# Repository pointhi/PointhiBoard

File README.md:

PointhiBoard
============

A Raspberry Pi board which is optimized for standalone robotic and automation applications

**Licence:** GNU GPLv3

**work status:** still in Developing

###Required Software

* Eagle V6 or higher
* XC8-Compiler from Microchip

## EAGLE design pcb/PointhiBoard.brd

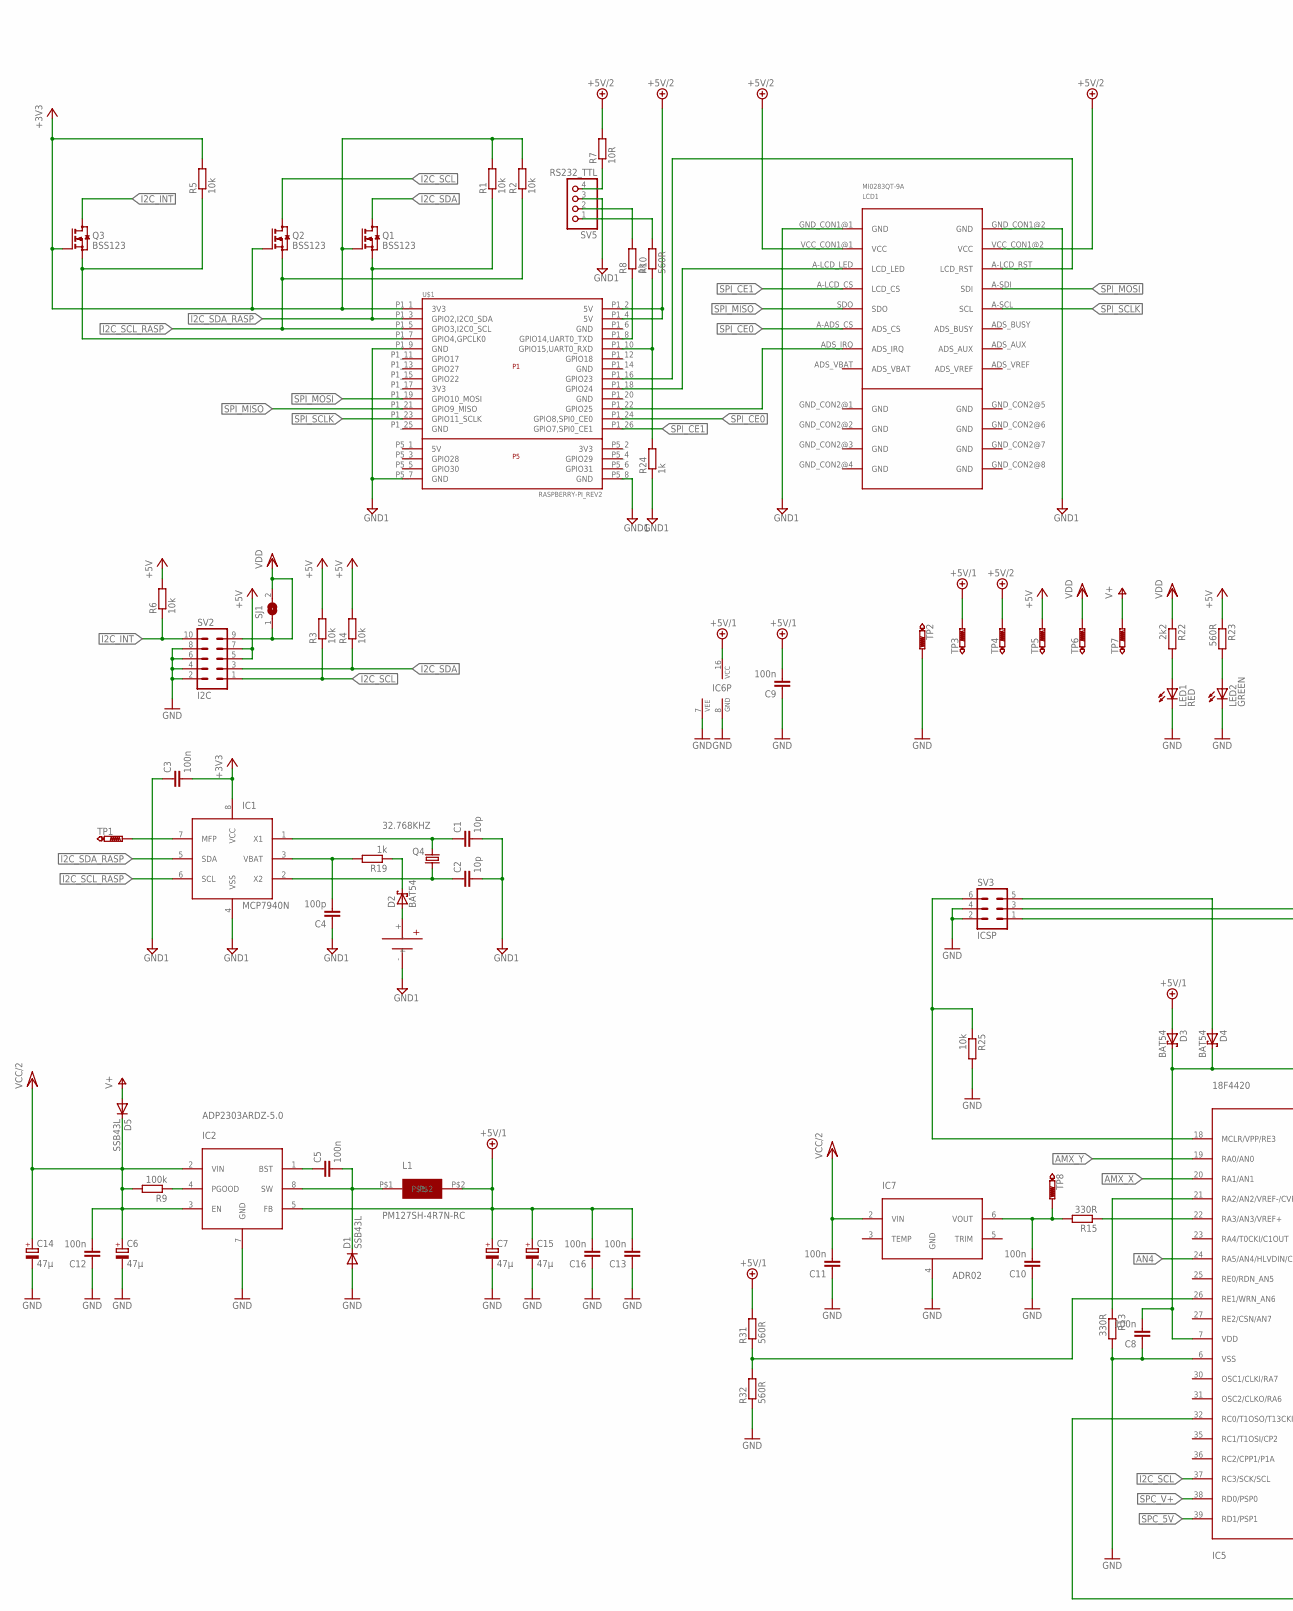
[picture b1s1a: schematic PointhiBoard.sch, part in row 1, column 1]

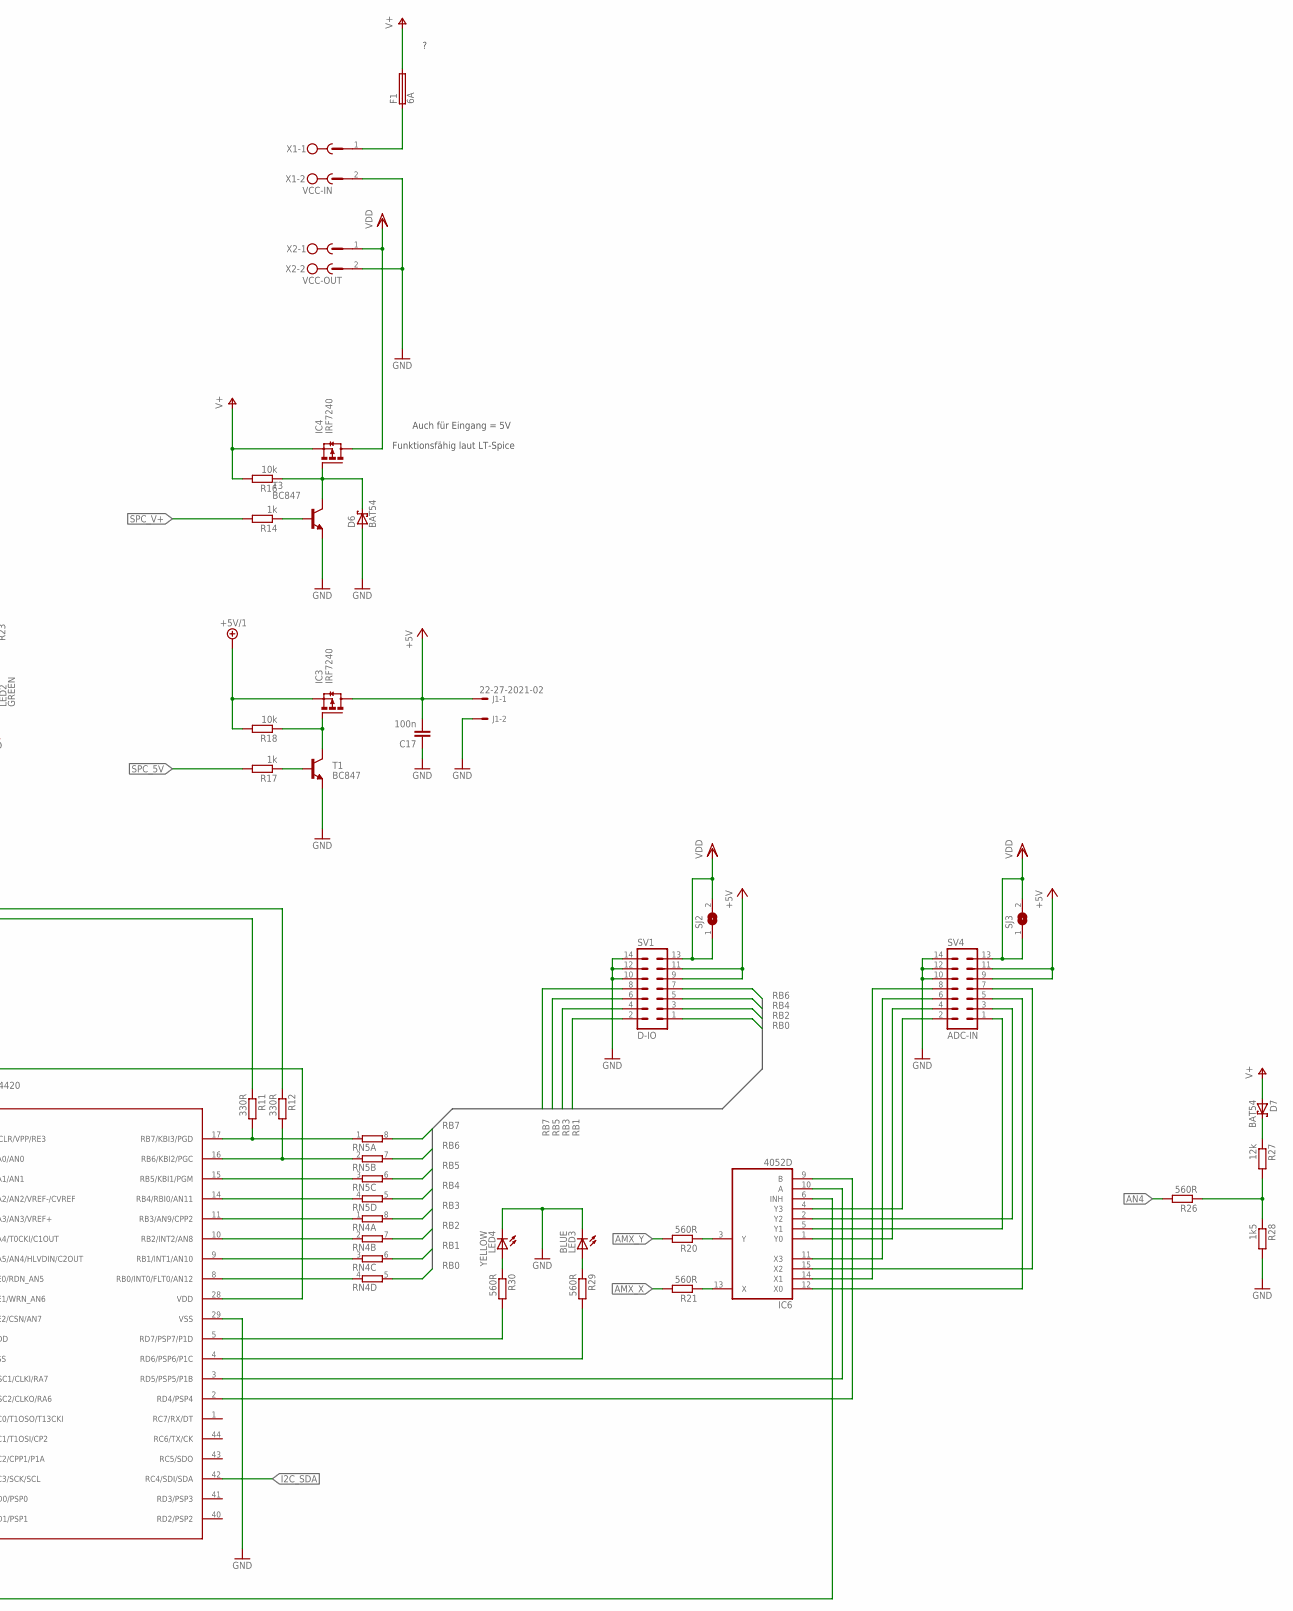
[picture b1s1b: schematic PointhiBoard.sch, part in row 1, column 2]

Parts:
BAT1: CH25-2032LF
C1, C2: 10p; C0805
C3, C5, C8, C9, C10, C11, C12, C13, C16, C17: 100n; C0805
C4: 100p; C0805
C6, C7, C14, C15: 47µ; PANASONIC_D
D1, D5: SSB43L; DO214AA
D2, D3, D4, D6, D7: BAT54; SOT23
F1: 6A; SHK20L
IC1: MCP7940N; MSOP8
IC2: ADP2303ARDZ-5.0; SOIC8
IC3, IC4: IRF7240; SOIC8
IC5: 18F4420; TQFP44
IC6: 4052D; SO16
IC7: ADR02; SOIC8
J1: 22-27-2021-02; 6410-02
L1: PM127SH-4R7N-RC; PM127SH
LCD1: MI0283QT-9A
LED1: RED; CHIP-LED0805
LED2: GREEN; CHIP-LED0805
LED3: BLUE; CHIP-LED0805
LED4: YELLOW; CHIP-LED0805
Q1, Q2, Q3: BSS123; SOT23
Q4: 32.768KHZ; MM20SS
R1, R2, R3, R4, R5, R6, R16, R18, R25: 10k; R0805
R7: 10R; R0805
R8, R14, R17, R19, R24: 1k; R0805
R9: 100k; R0805
R10, R20, R21, R23, R26, R29, R30, R31, R32: 560R; R0805
R11, R12, R13, R15: 330R; R0805
R22: 2k2; R0805
R27: 12k; R0805
R28: 1k5; R0805
RN4, RN5: 4R-NEXB38V; EXB38V
SJ1, SJ2, SJ3: SJ
SV1: D-IO; 3M_14L
SV2: I2C; 3M_10L
SV3: ICSP; ML6
SV4: ADC-IN; 3M_14L
SV5: RS232_TTL; 1X04
T1, T3: BC847; SOT23
TP1, TP2, TP3, TP4, TP5, TP6, TP7, TP8: PTR1B2,54; B2,54
U$1: RASPBERRY-PI_REV2
X1: VCC-IN; MSTBV2
X2: VCC-OUT; MSTBV2

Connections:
+3V3: C3.2, IC1.8 (VCC), Q1.1 (G), Q2.1 (G), Q3.1 (G), R1.2, R2.2, R5.2, U$1.P1_1 (3V3)
+5V: C17.2, IC3.5 (D), IC3.6 (D), IC3.7 (D), IC3.8 (D), J1.1, R3.2, R4.2, R6.2, R23.1, SV1.9, SV1.11, SV2.5, SV2.7, SV4.9, SV4.11, TP5.TP
+5V/1: C7.+, C9.2, C13.2, C15.+, C16.2, D3.1 (A), IC2.5 (FB), IC3.1 (S), IC3.2 (S), IC3.3 (S), IC6.16 (VCC), L1.P$2, R18.2, R31.2, TP3.TP
+5V/2: LCD1.VCC_CON1@1 (VCC), LCD1.VCC_CON1@2 (VCC), R7.2, TP4.TP, U$1.P1_2 (5V), U$1.P1_4 (5V)
AMX_X: IC5.20 (RA1/AN1), R21.2
AMX_Y: IC5.19 (RA0/AN0), R20.2
AN4: IC5.24 (RA5/AN4/HLVDIN/C2OUT), R26.2
GND: C6.-, C7.-, C8.1, C9.1, C10.1, C11.1, C12.1, C13.1, C14.-, C15.-, C16.1, C17.1, D1.A, D6.1 (A), IC2.7 (GND), IC5.6 (VSS), IC5.29 (VSS), IC6.7 (VEE), IC6.8 (GND), IC7.4 (GND), J1.2, LED1.C, LED2.C, LED3.C, LED4.C, R13.2, R25.2, R28.2, R32.1, SV1.10, SV1.12, SV1.14, SV2.2, SV2.4, SV2.6, SV2.8, SV3.2, SV3.4, SV4.10, SV4.12, SV4.14, T1.2 (E), T3.2 (E), TP2.TP, X1.2, X2.2
GND1: BAT1.-, C1.2, C2.2, C3.1, C4.1, IC1.4 (VSS), LCD1.GND_CON1@1 (GND), LCD1.GND_CON1@2 (GND), R24.1, SV5.3, U$1.P1_9 (GND), U$1.P5_7 (GND), U$1.P5_8 (GND)
I2C_INT: Q3.3 (D), R6.1, SV2.10
I2C_SCL: IC5.37 (RC3/SCK/SCL), Q2.3 (D), R3.1, SV2.1
I2C_SCL_RASP: IC1.6 (SCL), Q2.2 (S), R2.1, U$1.P1_5 (GPIO3,I2C0_SCL)
I2C_SDA: IC5.42 (RC4/SDI/SDA), Q1.3 (D), R4.1, SV2.3
I2C_SDA_RASP: IC1.5 (SDA), Q1.2 (S), R1.1, U$1.P1_3 (GPIO2,I2C0_SDA)
MCLR: IC5.18 (MCLR/VPP/RE3), R25.1, SV3.6
unnamed: Q3.2 (S), R5.1, U$1.P1_7 (GPIO4,GPCLK0)
unnamed: LCD1.A-LCD_LED (LCD_LED), U$1.P1_18 (GPIO24)
unnamed: LCD1.A-LCD_RST (LCD_RST), U$1.P1_16 (GPIO23)
unnamed: LCD1.ADS_IRQ, U$1.P1_22 (GPIO25)
unnamed: R7.1, SV5.4
unnamed: R8.1, U$1.P1_8 (GPIO14,UART0_TXD)
unnamed: R8.2, SV5.2
unnamed: C5.2, D1.C, IC2.8 (SW), L1.P$1
unnamed: C8.2, D3.3 (C), D4.3 (C), IC5.7 (VDD), IC5.28 (VDD)
unnamed: C5.1, IC2.1 (BST)
unnamed: IC2.4 (PGOOD), R9.1
unnamed: IC5.17 (RB7/KBI3/PGD), R11.2, RN5.1
unnamed: IC5.16 (RB6/KBI2/PGC), R12.2, RN5.2 (1)
unnamed: C1.1, IC1.1 (X1), Q4.1
unnamed: C2.1, IC1.2 (X2), Q4.4 (2)
unnamed: D6.3 (C), IC4.4 (G), R16.1, T3.3 (C)
unnamed: R14.1, T3.1 (B)
unnamed: IC1.7 (MFP), TP1.TP
unnamed: IC5.15 (RB5/KBI1/PGM), RN5.3 (1)
unnamed: IC3.4 (G), R18.1, T1.3 (C)
unnamed: R17.1, T1.1 (B)
unnamed: IC5.14 (RB4/RBI0/AN11), RN5.4 (1)
unnamed: IC5.11 (RB3/AN9/CPP2), RN4.1
unnamed: F1.1A (1), X1.1
unnamed: IC5.10 (RB2/INT2/AN8), RN4.2 (1)
unnamed: IC5.9 (RB1/INT1/AN10), RN4.3 (1)
unnamed: IC5.8 (RB0/INT0/FLT0/AN12), RN4.4 (1)
unnamed: D4.1 (A), SV3.5
unnamed: C4.2, IC1.3 (VBAT), R19.2
unnamed: BAT1.+, D2.1 (A)
unnamed: D2.3 (C), R19.1
unnamed: D7.3 (C), R27.1
unnamed: R11.1, SV3.1
unnamed: R12.1, SV3.3
unnamed: IC6.1 (Y0), SV4.4
unnamed: IC6.2 (Y2), SV4.3
unnamed: IC6.4 (Y3), SV4.2
unnamed: IC6.5 (Y1), SV4.1
unnamed: IC6.15 (X2), SV4.7
unnamed: IC6.14 (X1), SV4.8
unnamed: IC6.12 (X0), SV4.5
unnamed: IC6.11 (X3), SV4.6
unnamed: IC5.3 (RD5/PSP5/P1B), IC6.10 (A)
unnamed: IC5.2 (RD4/PSP4), IC6.9 (B)
unnamed: IC5.32 (RC0/T1OSO/T13CKI), IC6.6 (INH)
unnamed: C10.2, IC7.6 (VOUT), R15.2, TP8.TP
unnamed: IC5.22 (RA3/AN3/VREF+), R15.1
unnamed: IC5.21 (RA2/AN2/VREF-/CVREF), R13.1
unnamed: IC6.13 (X), R21.1
unnamed: IC6.3 (Y), R20.1
unnamed: LED1.A, R22.2
unnamed: LED2.A, R23.2
unnamed: R10.1, R24.2, U$1.P1_10 (GPIO15,UART0_RXD)
unnamed: R10.2, SV5.1
unnamed: R26.1, R27.2, R28.1
unnamed: IC5.4 (RD6/PSP6/P1C), R29.2
unnamed: IC5.26 (RE1/WRN_AN6), R31.1, R32.2
unnamed: IC5.5 (RD7/PSP7/P1D), R30.2
unnamed: LED3.A, R29.1
unnamed: LED4.A, R30.1
RB0: RN4.5 (2), SV1.1
RB1: RN4.6 (2), SV1.2
RB2: RN4.7 (2), SV1.3
RB3: RN4.8 (2), SV1.4
RB4: RN5.5 (2), SV1.5
RB5: RN5.6 (2), SV1.6
RB6: RN5.7 (2), SV1.7
RB7: RN5.8 (2), SV1.8
SPC_5V: IC5.39 (RD1/PSP1), R17.2
SPC_V+: IC5.38 (RD0/PSP0), R14.2
SPI_CE0: LCD1.A-ADS_CS (ADS_CS), U$1.P1_24 (GPIO8,SPI0_CE0)
SPI_CE1: LCD1.A-LCD_CS (LCD_CS), U$1.P1_26 (GPIO7,SPI0_CE1)
SPI_MISO: LCD1.SDO, U$1.P1_21 (GPIO9_MISO)
SPI_MOSI: LCD1.A-SDI (SDI), U$1.P1_19 (GPIO10_MOSI)
SPI_SCLK: LCD1.A-SCL (SCL), U$1.P1_23 (GPIO11_SCLK)
V+: D5.A, D7.1 (A), F1.2A (2), IC4.1 (S), IC4.2 (S), IC4.3 (S), R16.2, TP7.TP
VCC/2: C6.+, C11.2, C12.2, C14.+, D5.C, IC2.2 (VIN), IC2.3 (EN), IC7.2 (VIN), R9.2
VDD: IC4.5 (D), IC4.6 (D), IC4.7 (D), IC4.8 (D), R22.1, SJ1.1, SJ1.2, SJ2.1, SJ2.2, SJ3.1, SJ3.2, SV1.13, SV2.9, SV4.13, TP6.TP, X2.1

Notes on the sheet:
Funktionsfähig laut LT-Spice
Auch für Eingang = 5V

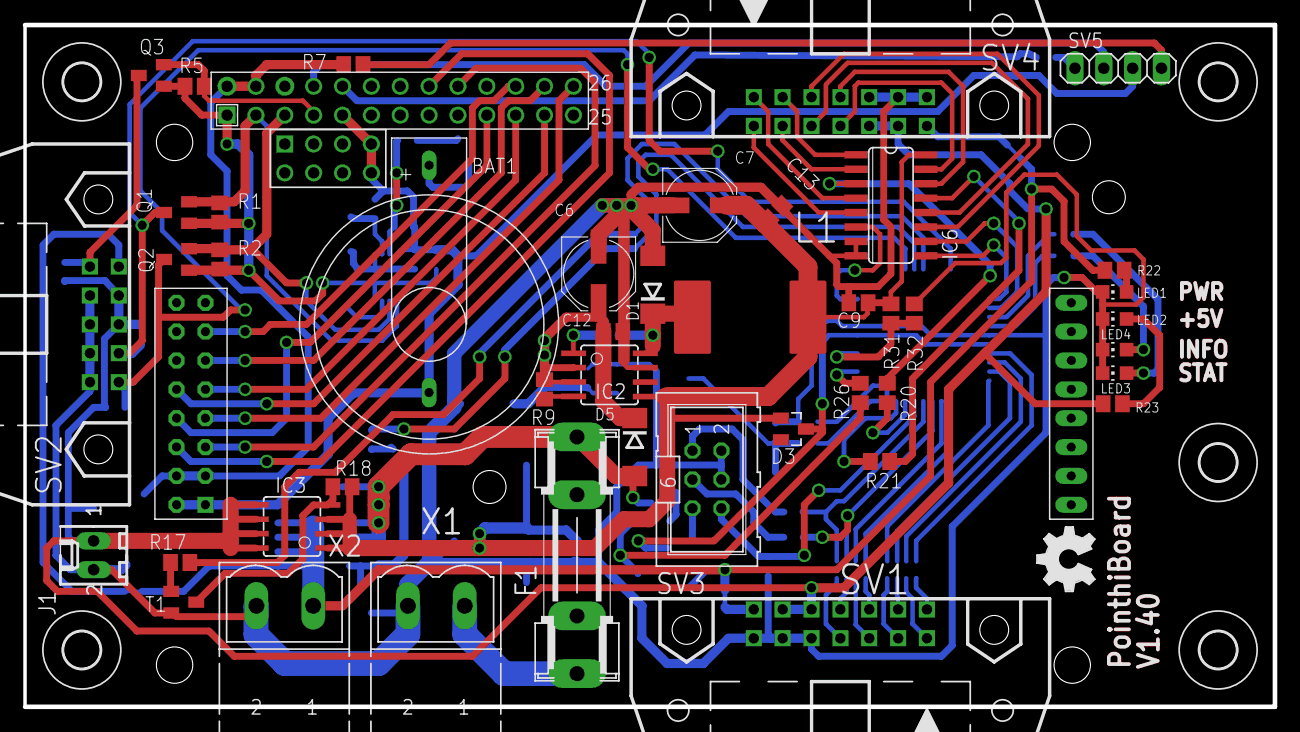
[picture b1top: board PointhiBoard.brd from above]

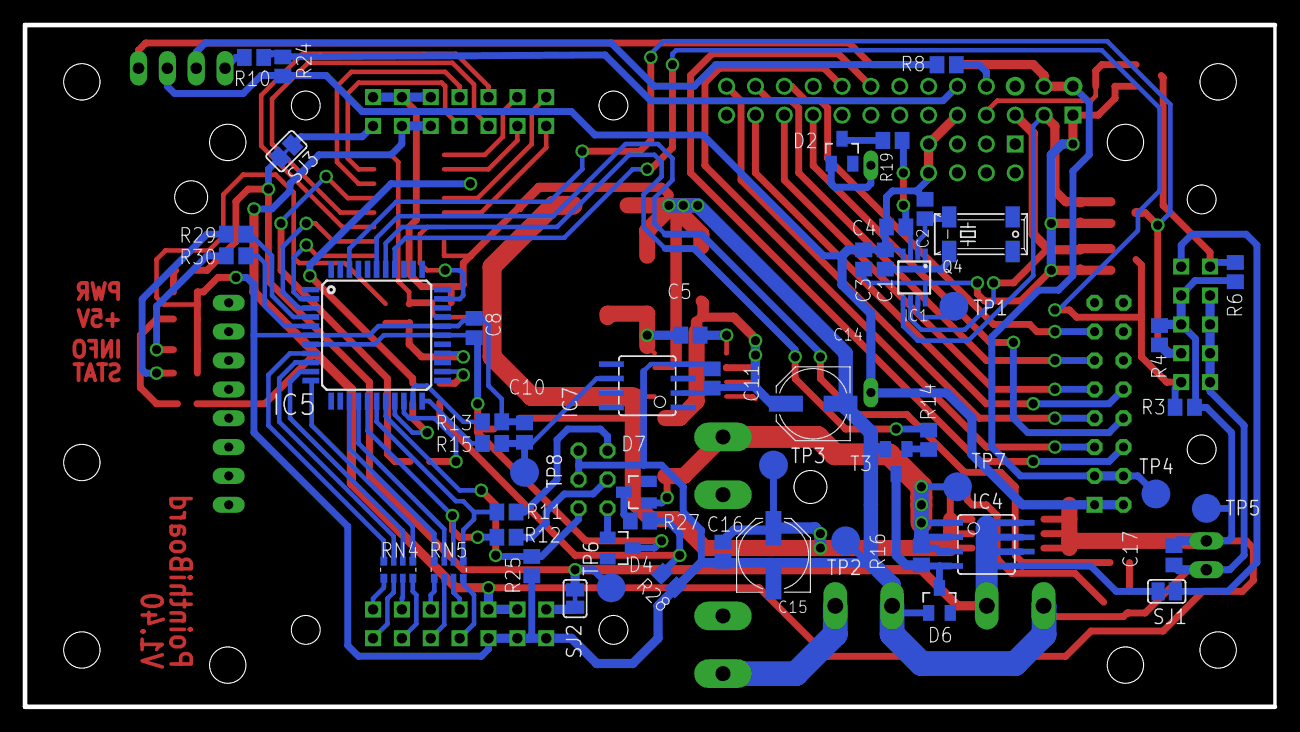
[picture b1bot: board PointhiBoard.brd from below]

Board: 2 copper layers, 110.0 x 60.0 mm, 105 parts (53 on the bottom side), 93 nets.

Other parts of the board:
U$2, U$3, U$4, U$5, U$6: 3,2
U$7: OSHW_FILLX200_NOTEXT

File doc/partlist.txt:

Part                Value           Package

BAT1                CH25-2032LF     CH25-2032LF
C1,C2               10p             C0805
C3,C4,C5,C8,C9,C10  100n            C0805
V11,C12,C13,C16,C17 100n            C0805
C6,C7,C14,C15       47µ             PANASONIC_D
D1                  SSB43L          DO214AA
D2,D3,D4,D6,D7      BAT54           SOT23
D5                  SSB43L          DO214AA
F1                  6A              SHK20L
IC1                 MCP7940N        MSOP8
IC2                 ADP2303ARDZ-5.0 SOIC8
IC3,IC4             IRF7240         SOIC8
IC5                 18F4420         TQFP44
IC6                 4052D           SO16
IC7                 ADR02           SOIC8
J1                  22-27-2021-02   6410-02
L1                  PM127SH-4R7N-RC PM127SH
LCD1                MI0283QT-9A     MI0283QT-9A #TODO
LED1                RED             CHIP-LED0805
LED2                GREEN           CHIP-LED0805
LED3                BLUE            CHIP-LED0805
LED4                YELLOW          CHIP-LED0805
Q1,Q2,Q3            BSS123          SOT23
Q4                  32.768KHZ       MM20SS
R7                  10R             R0805
R11,R12,R13,R15     330R            R0805
R10,R20,R21,R23,R26 560R            R0805
R29,R30,R31,R32     560R            R0805
R8,R14,R17,R19,R24  1k              R0805
R28                 1k5             R0805
R22                 2k2             R0805
R1,R2,R3,R4,R5,R6   10k             R0805
R16,R18,R25         10k             R0805
R27                 12k             R0805
R9                  100k            R0805
RN4,RN5             EXB38V          resistor-dil
SJ1,SJ2,SJ3         SJ              jumper
SV2                 I2C             3M_10L
SV1                 D-IO            3M_14L
SV4                 ADC-IN          3M_14L
SV3                 ICSP            ML6
SV5                 RS232_TTL       1X04
T1,T3               BC847           SOT23
X1                  VCC-IN          MSTBV2
X2                  VCC-OUT         MSTBV2

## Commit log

2014-03-01 adding current files
2014-03-01 update project
2014-03-02 fix wrong adc-port, little layout modifies
2014-03-29 Adding full ADC-Support
2014-03-29 adding test-function and Interrupt driven timer-function
2014-03-29 optimize code
2014-03-30 little fix
2014-04-10 fix adc
    ADC is now working correctly
2014-04-10 Add Set and Get-Function for PORTB
2014-04-12 Initial working I2C-Implementation
2014-04-12 add via i2c set and readeable registers
2014-04-23 using .tex instead of .odt for documentation
2014-04-23 upload .pdf of current german-documentation
2014-04-23 update German Documentation
2014-04-23 Adding image of boot-screen to readme.md
2014-04-24 fix position and orentation of text(values, names,...) on the pcb
2014-04-24 fix hole-diameter of con-harting-ml
2014-04-24 fix warnings on pcb
2014-05-22 adding simple library and example-code to work with the board
2014-07-06 update documentation
2014-07-06 update library name
2014-07-06 update example-code
2014-07-06 update pcb
